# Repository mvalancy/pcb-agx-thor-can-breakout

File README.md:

<picture>
  <source media="(prefers-color-scheme: dark)" srcset="docs/img/hero/pcb-agx-thor-can-breakout-dark.svg">
  
</picture>

# Thor CAN breakout

Passive CAN adapters and printable housings for NVIDIA Jetson AGX Thor. The adapter brings the carrier's CAN bus signals to male DE9 connectors and the remaining J47 signals to an internal I/O header.

[Design review](docs/design-review.md) · [Design packages](releases/README.md) · [Termination & prototyping](docs/termination-and-io.md) · [Assembly guide](ASSEMBLY.md) · [Manufacturing guide](docs/manufacturing.md) · [Validation and open gates](docs/release-checklist.md) · [Local review page](http://localhost:8765/site/)

**A1 engineering prototype — not production qualified.** Both boards pass electrical CAD checks, and the housings pass modeled collision, assembly-path and mesh checks. No physical board or housing has been tested. The exact ribbon/header mating, supplier assembly, CAN operation and transient protection must be verified before connecting an expensive host or ordering 50 units.

## PINOUT proof

© NVIDIA. Direct excerpt from **P4071 A02 concept schematic, sheet 11**. J47 is **Wieson AC2800-0011-022-H0**; read the external contact numbers beside the wires. [Source and capture provenance](docs/pinout-proof.md).

© NVIDIA. The [Jetson Linux r38.2 CAN guide](https://docs.nvidia.com/jetson/archives/r38.2/DeveloperGuide/HR/ControllerAreaNetworkCan.html) independently identifies **CAN0 H/L = 3/5**, **CAN1 H/L = 7/9**, and termination bridges **3–4 / 7–8**. [Full proof, auxiliary mapping and limits](docs/pinout-proof.md). These sources establish documented pins; actual carrier population and all 26 cable conductors still require verification.

## What it does

- Uses the same Wieson **AC2800-0011-022-H0** header identified in Thor's P4071 A02 BOM. Its 26-pad footprint is recovered from NVIDIA's native layout.
- Routes CAN directly to standard CAN DE9 pins: **2 = CAN-L, 7 = CAN-H, 3/6 = ground, 5/shell = shield**. Pins 1/4/8/9 are unconnected; pin 9 supplies no power.
- Adds a **Bourns CDSOT23-SM712 TVS** to each channel. This is a passive breakout, not an isolated repeater or a transceiver board.
- Enables the carrier’s existing **120 Ω termination with JP1 (CAN0) and JP2 (CAN1)**; fit a 2.54 mm jumper cap only at a bus endpoint. Auxiliary power and shield links also remain **open by default**. [Illustrated setup](docs/termination-and-io.md).
- Retains all 26 header signals and adds isolated 2.54 mm prototyping grids, ground and gated 3.3 V/5 V taps. Raw FSI GPIO is firmware-dependent, not a normal Linux GPIO.
- Houses the PCB with heat-set inserts, recessed screw heads, a keyed seam, four broad, recessed M3 corner mounting ears and a padded ribbon clamp with filleted rear supports. The lid carries the pinout, port names, A1 revision and `github.com/mvalancy`.

The TVS is intended to reduce transients; the assembly has no verified surge rating and does not protect against sustained 24 V miswiring. Raw auxiliary I/O has no added protection. See [electrical scope](docs/interface-and-protection.md).

## Choose the right variant

| | Two-port | Four-port engineering variant |
|---|---|---|
| Intended use | AGX Thor FSI CAN0/CAN1 | Generic P4071 A02 full-header investigation |
| Extra channels | Retained on internal J11 for investigation | External ports marked RES2/RES3 |
| IGX compatibility | Not established | **Not established; do not infer it from AURIX net names** |
| PCB | 93 × 90 mm | 177 × 90 mm |
| Housing | 103.2 × 114.2 × 26.8 mm | 187.2 × 114.2 × 26.8 mm |
| Including mounting ears | 149.2 × 114.2 × 26.8 mm | 233.2 × 114.2 × 26.8 mm |
| Prototype pads | 120 isolated pads + gated power taps | 324 isolated pads + gated power taps |
| Schematic | [PDF](exports/2port/schematic.pdf) | [PDF](exports/4port/schematic.pdf) |
| Copper | [Top](exports/2port/pcb-top.svg) · [Bottom](exports/2port/pcb-bottom.svg) | [Top](exports/4port/pcb-top.svg) · [Bottom](exports/4port/pcb-bottom.svg) |
| Native KiCad project | [Two-port](hardware/2port/thor-2port.kicad_pro) | [Four-port](hardware/4port/thor-4port.kicad_pro) |
| Assembly | [Drawing](exports/2port/assembly.svg) · [BOM](exports/2port/bom-review.csv) | [Drawing](exports/4port/assembly.svg) · [BOM](exports/4port/bom-review.csv) |
| Housing dimensions | [Plan](exports/2port/enclosure-plan.svg) | [Plan](exports/4port/enclosure-plan.svg) |
| Check reports | [Electrical](exports/2port/pcb-evidence.json) · [Mechanical](exports/2port/mechanical-checks.json) | [Electrical](exports/4port/pcb-evidence.json) · [Mechanical](exports/4port/mechanical-checks.json) |

The extra channels in the generic schematic do not prove that a particular AGX or IGX carrier populates or supports them. [Carrier compatibility research](research/igx-compatibility.md).

## Termination and room to build

[Termination, AUX pinout, FSI_EXT_GPIO1 limits and prototype wiring](docs/termination-and-io.md) explains every control and usable area. Both power rails stay disconnected until their individual enable shunts are fitted.

## Header, ribbon cable and mating connectors

The cable candidate is **Samtec FFSD-13-D-06.00-01-N**, 152.4 mm long, with two 26-position female connectors: [DigiKey SAM8785-ND](https://www.digikey.com/en/products/detail/samtec-inc/FFSD-13-D-06-00-01-N/3190987). Its fit on the actual Wieson header and pin-for-pin continuity are not yet verified. Do not treat the Samtec SHF alternative footprint as an approved Wieson substitute. [Header audit](research/j47-footprint-audit.md).

The board DE9 is **Assmann A-DS 09 A/KG-T2S / C3127392**. Mating clearance models represent **A-DF 09 LL/Z** female connectors with **A-FT 09** backshells and #4-40 thumbscrews. At 42 mm port pitch, maximum-width hood envelopes leave 7.7 mm between neighbors. Actual screw engagement and hood capture still require a sample. [Connector sourcing](research/connector-sourcing.md) · [Mating audit](research/mating-dsub-clearance.md).

## Print and assemble

The lid uses bold lettering throughout, 4 mm body-text size, enlarged pin numbers and 1 mm diagram strokes. The 0.4 mm recesses retain 2 mm of roof underneath. [Lid layout and clearance evidence](docs/enclosure.md) explain the dimensions and print assumptions; renders show optional light paint fill.

Use one matching base/lid pair and the common ribbon clamp. Print the insert/counterbore and port coupons first. The [assembly guide](ASSEMBLY.md) and [hardware BOM](exports/enclosure-bom.csv) specify six heat-set inserts, four M3 × 20 lid screws, two M3 × 6 clamp screws, PCB washers and silicone pads.

| Printed part | STL | Quantity |
|---|---|---:|
| Two-port base/lid | [Base](exports/2port_base.stl) · [Lid](exports/2port_lid.stl) | One each for two-port |
| Four-port base/lid | [Base](exports/4port_base.stl) · [Lid](exports/4port_lid.stl) | One each for four-port |
| Common ribbon clamp | [Clamp](exports/ribbon_clamp.stl) | 1 |
| Insert/counterbore coupon | [Coupon](exports/fastener_coupon.stl) | Test first |
| DE9 opening coupon | [Coupon](exports/port_coupon.stl) | Test first |

[STEP and 3MF files](exports/README.md) are also supplied. STL/3MF files are bed-oriented; STEP files use assembly coordinates. Mounting ears are 26 mm wide with R4 roots and retain 7 mm thickness. Four M3 holes form a 123.2 × 76 mm pattern on the two-port base or 207.2 × 76 mm on the four-port base. The proposed 10 N / 60 s cable pull test has not been performed. White paint fill is optional and is shown in the renders.

## Manufacturing and release status

**A1 development is published on `main`.** Improvements use development branches and pull requests; merged feature branches are deleted, and plain `dev` follows `main`. Review packages are produced locally and by PR CI. Existing [A0 releases](https://github.com/mvalancy/pcb-agx-thor-can-breakout/releases) are historical and superseded: A1 corrects the CAN pair routing and the enclosure's PCB handedness. Use PCB and housing files from the same commit/manifest. The current 90 mm-deep design also supersedes earlier 65 mm A1 development drafts. [Package structure](releases/README.md).

The [JLCPCB guide](docs/manufacturing.md) explains the Gerber/drill ZIP, SMT-only BOM/CPL and full sourced BOM/CPL. **J1 Wieson procurement/consignment is unresolved**, so this is not a complete turnkey PCBA order. Review placements and supplier DFM before ordering prototypes. No purchase has been made.

Start with 3–5 prototypes. Validate mating and continuity while disconnected from Thor, then check CAN communication, intended bitrates, grounding, protection and housing retention. Proceed toward approximately 50 units only after the [release checklist](docs/release-checklist.md) is closed.

## Local review and reproduction

The [localhost review page](http://localhost:8765/site/) embeds schematic PDFs, PCB layers, dimensions, lid drawings, 3D assemblies and check reports. This link works on the machine running the server; it is not a public web deployment. The site imports the reusable [cad-agent](https://github.com/Valpatel/cad-agent) tools, including the shared finer wheel zoom (four increments cover the former one-increment distance).

Use Python 3.11 or newer, KiCad 10.0.1 and the pinned dependencies. The recorded build used Python 3.12.3; KiCad's Python environment separately supplies `pcbnew`. See the [toolchain record](references/toolchain.json).

```bash
python3 -m venv .venv
.venv/bin/pip install -r requirements.txt
.venv/bin/cad-agent site --serve --port 8765
```

To rebuild and validate the committed routed design:

```bash
.venv/bin/python tools/export_review.py
.venv/bin/python tools/check_electronics.py
# Also run check_can_routing.py, check_fabrication.py and check_prototype.py with KiCad Python.
.venv/bin/python cad/build.py
.venv/bin/python tools/check_mechanics.py
.venv/bin/python tools/check_lid_markings.py
.venv/bin/python tools/render_review.py
.venv/bin/python tools/draw_mechanics.py
.venv/bin/python tools/draw_controls.py
.venv/bin/cad-agent export-3mf
.venv/bin/cad-agent holes
.venv/bin/cad-agent overhangs
.venv/bin/cad-agent inserts cad/joints.yaml --output exports/inserts.json
.venv/bin/cad-agent slice
.venv/bin/python tools/check_lid_slicing.py
.venv/bin/cad-agent view
.venv/bin/python tools/update_evidence.py
.venv/bin/cad-agent report
.venv/bin/python tools/write_readmes.py
.venv/bin/python tools/validate_release.py --record
.venv/bin/python tools/package_release.py
```

`tools/build_electronics.py` regenerates native sources and overwrites layouts unless `--schematic-only` is used. Full electrical regeneration also requires routing, finalization and all checks. [Tool instructions](tools/README.md) · [Iteration history](docs/iterations.md).

## Project structure

| Folder | Contents |
|---|---|
| [hardware](hardware/README.md) | KiCad projects, interface pin map and pinned footprints |
| [cad](cad/README.md) | Parametric housing source and dimensions |
| [exports](exports/README.md) | Manufacturing review, drawing, print and validation files |
| [preview](preview/README.md) | Rendered assembly and lid views |
| [docs](docs/README.md) | Manufacturing, qualification, decisions and progress |
| [research](research/README.md) | Connector and carrier evidence |
| [references](references/README.md) | Source register and toolchain; vendor archives excluded |
| [tools](tools/README.md) | Generation, checks and release packaging |
| [releases](releases/README.md) | Package structure and release notes |
| [.agents](.agents/README.md) | Engineering lessons and review procedures |
| [.github/workflows](.github/workflows/README.md) | CI and prerelease publication |

Folders have READMEs except `.github` itself: GitHub prioritizes its README over this project overview. CI documentation lives in `.github/workflows/README.md`, and validation prevents recreating the overriding index.

## License

Original work is [MIT licensed](LICENSE). KiCad library derivatives retain CC BY-SA 4.0 and the KiCad design exception; see [third-party notices](THIRD_PARTY.md). Full vendor PDFs and logos are not redistributed. The attributed NVIDIA pinout excerpts retain NVIDIA rights and are excluded from the MIT grant. This project is not affiliated with NVIDIA, Samtec, Assmann or JLCPCB.

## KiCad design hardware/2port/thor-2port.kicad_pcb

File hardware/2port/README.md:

<!-- generated by tools/write_readmes.py -->
# 2-port KiCad project

[Project overview](../../README.md) · [Documentation](../../docs/README.md) · [Local design review](http://localhost:8765/site/)

Native source for the documented AGX Thor FSI CAN0/CAN1 interface.

[Open in KiCad](thor-2port.kicad_pro) · [Schematic PDF](../../exports/2port/schematic.pdf) · [Review exports](../../exports/2port/README.md)

The project includes the schematic, routed board, local symbol/footprint tables and native fabrication rules. `evidence-manifest.json` binds checks to these sources. Review the [pinout proof](../../docs/pinout-proof.md) and [protection scope](../../docs/interface-and-protection.md) before modifying the interface.

CAN trunks use 0.25 mm copper with 0.25 mm straight-section spacing and a protected bottom return corridor. This two-layer/ribbon assembly is not controlled 120 Ω impedance or qualified for a maximum data rate. All removable links are open by default.

<details>
<summary>Complete folder index</summary>

| File or folder | Purpose |
|---|---|
| [Thor.kicad_sym](Thor.kicad_sym) | Pinned schematic symbols |
| [evidence-manifest.json](evidence-manifest.json) | Machine-readable design evidence |
| [fp-lib-table](fp-lib-table) | Project support file |
| [sym-lib-table](sym-lib-table) | Project support file |
| [thor-2port.kicad_dru](thor-2port.kicad_dru) | Native fabrication rules |
| [thor-2port.kicad_pcb](thor-2port.kicad_pcb) | Routed native board |
| [thor-2port.kicad_pro](thor-2port.kicad_pro) | KiCad project settings |
| [thor-2port.kicad_sch](thor-2port.kicad_sch) | Native schematic |

</details>

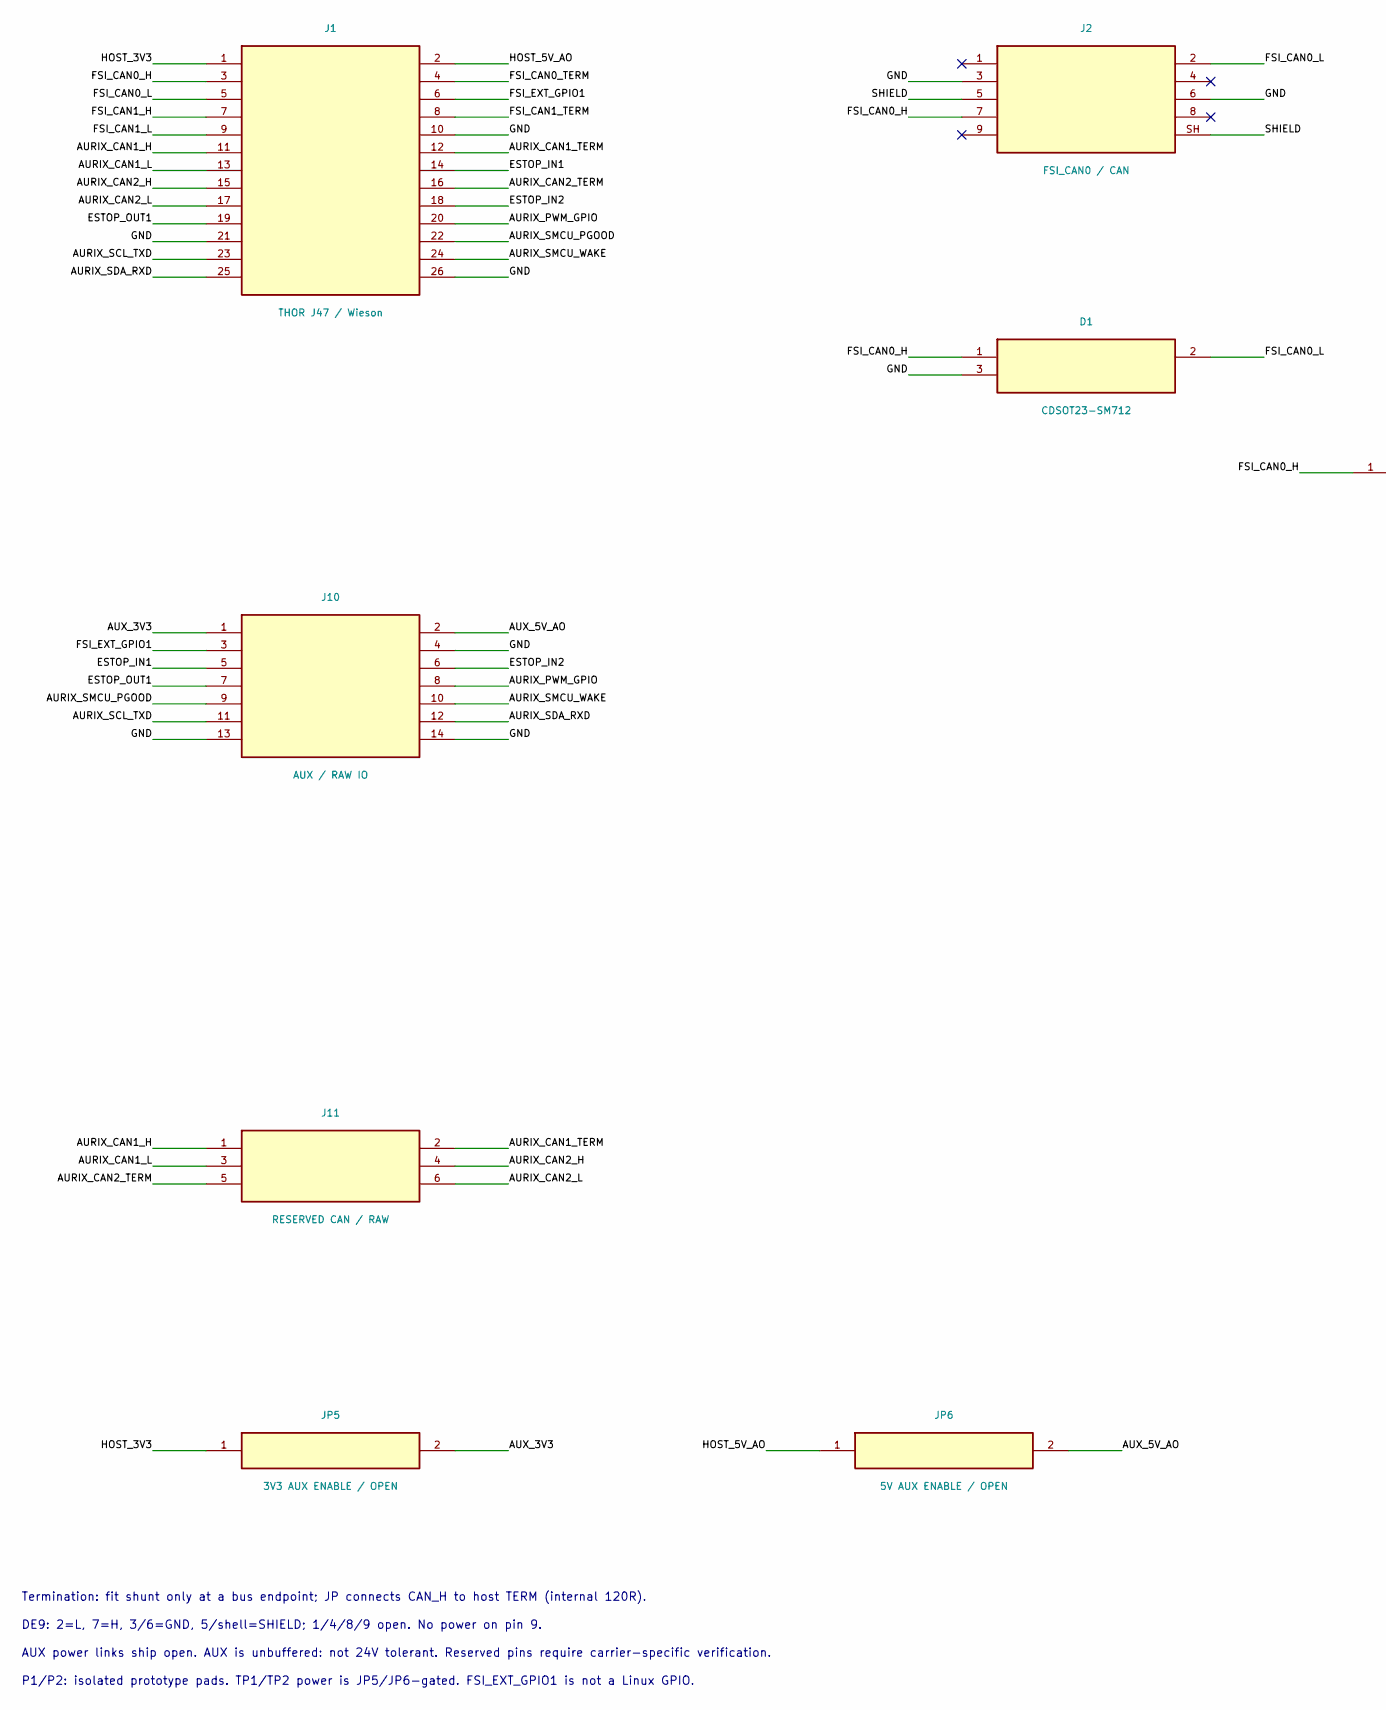
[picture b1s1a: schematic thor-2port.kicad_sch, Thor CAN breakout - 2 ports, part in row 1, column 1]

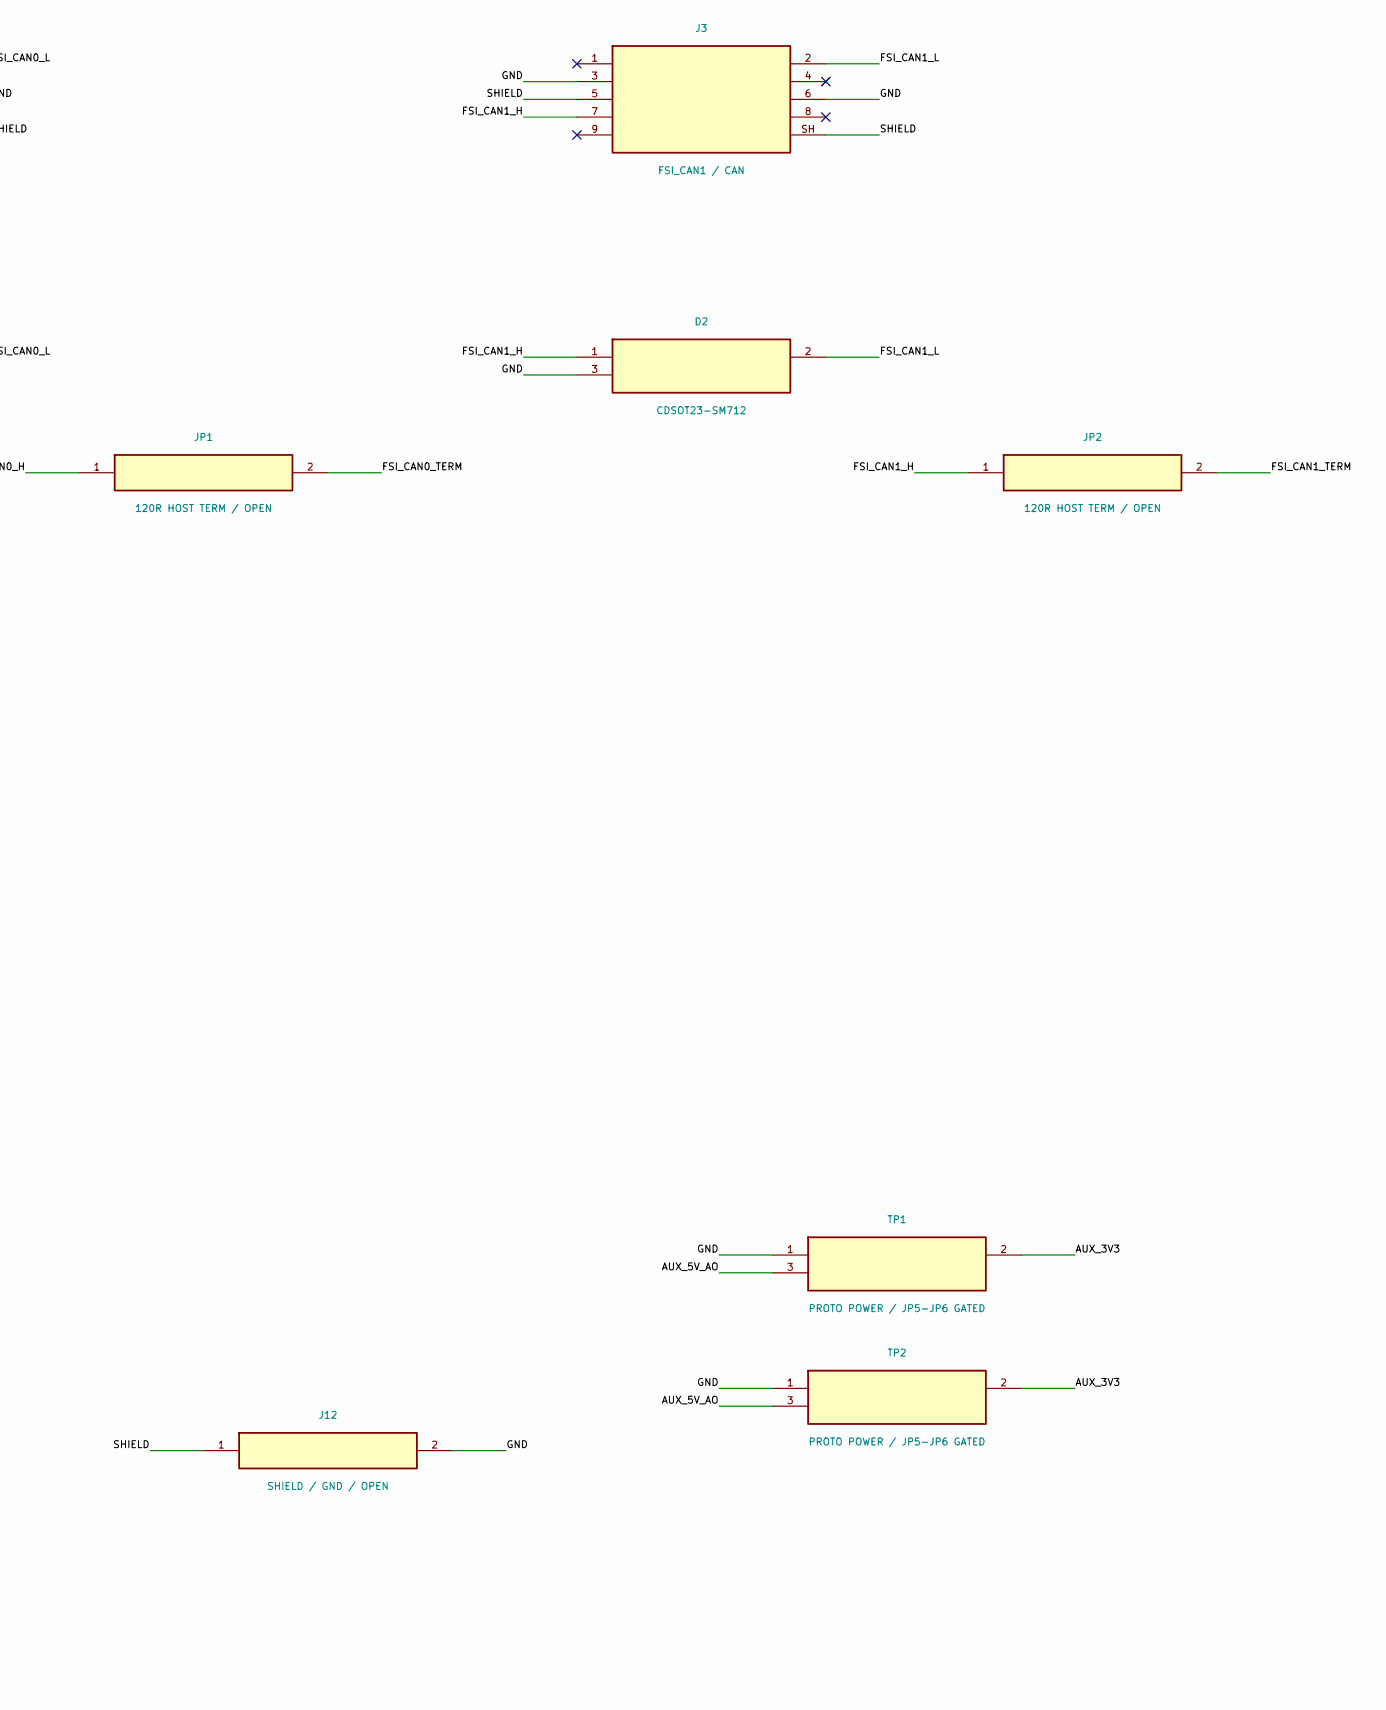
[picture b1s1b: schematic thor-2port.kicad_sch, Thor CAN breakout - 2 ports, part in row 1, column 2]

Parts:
D1, D2: CDSOT23-SM712; SOT-23; MPN CDSOT23-SM712; LCSC C404012
J1: THOR J47 / Wieson; Wieson_AC2800-0011-022-H0; MPN AC2800-0011-022-H0
J2: FSI_CAN0 / CAN; Assmann_A-DS_09_A-KG-T2S; MPN A-DS 09 A/KG-T2S; LCSC C3127392
J3: FSI_CAN1 / CAN; Assmann_A-DS_09_A-KG-T2S; MPN A-DS 09 A/KG-T2S; LCSC C3127392
J10: AUX / RAW IO; PinHeader_2x07_P2.54mm_Vertical; MPN BOOMELE 2.54-2x7P male C71397; LCSC C71397
J11: RESERVED CAN / RAW; PinHeader_2x03_P2.54mm_Vertical; MPN BOOMELE 2.54-2x3P male C65114; LCSC C65114
J12: SHIELD / GND / OPEN; XFCN_PZ254V-11-02P; MPN PZ254V-11-02P; LCSC C492401
JP1, JP2: 120R HOST TERM / OPEN; XFCN_PZ254V-11-02P; MPN PZ254V-11-02P; LCSC C492401
JP5: 3V3 AUX ENABLE / OPEN; XFCN_PZ254V-11-02P; MPN PZ254V-11-02P; LCSC C492401
JP6: 5V AUX ENABLE / OPEN; XFCN_PZ254V-11-02P; MPN PZ254V-11-02P; LCSC C492401
TP1, TP2: PROTO POWER / JP5-JP6 GATED; Prototype_Power_3x3_P2.54

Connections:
/AURIX_CAN1_H: J1.11 (AURIX_CAN1_H), J11.1 (AURIX_CAN1_H)
/AURIX_CAN1_L: J1.13 (AURIX_CAN1_L), J11.3 (AURIX_CAN1_L)
/AURIX_CAN1_TERM: J1.12 (AURIX_CAN1_TERM), J11.2 (AURIX_CAN1_TERM)
/AURIX_CAN2_H: J1.15 (AURIX_CAN2_H), J11.4 (AURIX_CAN2_H)
/AURIX_CAN2_L: J1.17 (AURIX_CAN2_L), J11.6 (AURIX_CAN2_L)
/AURIX_CAN2_TERM: J1.16 (AURIX_CAN2_TERM), J11.5 (AURIX_CAN2_TERM)
/AURIX_PWM_GPIO: J1.20 (AURIX_PWM_GPIO), J10.8 (AURIX_PWM_GPIO)
/AURIX_SCL_TXD: J1.23 (AURIX_SCL_TXD), J10.11 (AURIX_SCL_TXD)
/AURIX_SDA_RXD: J1.25 (AURIX_SDA_RXD), J10.12 (AURIX_SDA_RXD)
/AURIX_SMCU_PGOOD: J1.22 (AURIX_SMCU_PGOOD), J10.9 (AURIX_SMCU_PGOOD)
/AURIX_SMCU_WAKE: J1.24 (AURIX_SMCU_WAKE), J10.10 (AURIX_SMCU_WAKE)
/AUX_3V3: J10.1 (AUX_3V3), JP5.2 (AUX_3V3), TP1.2 (AUX_3V3), TP2.2 (AUX_3V3)
/AUX_5V_AO: J10.2 (AUX_5V_AO), JP6.2 (AUX_5V_AO), TP1.3 (AUX_5V_AO), TP2.3 (AUX_5V_AO)
/ESTOP_IN1: J1.14 (ESTOP_IN1), J10.5 (ESTOP_IN1)
/ESTOP_IN2: J1.18 (ESTOP_IN2), J10.6 (ESTOP_IN2)
/ESTOP_OUT1: J1.19 (ESTOP_OUT1), J10.7 (ESTOP_OUT1)
/FSI_CAN0_H: D1.1 (FSI_CAN0_H), J1.3 (FSI_CAN0_H), J2.7 (FSI_CAN0_H), JP1.1 (FSI_CAN0_H)
/FSI_CAN0_L: D1.2 (FSI_CAN0_L), J1.5 (FSI_CAN0_L), J2.2 (FSI_CAN0_L)
/FSI_CAN0_TERM: J1.4 (FSI_CAN0_TERM), JP1.2 (FSI_CAN0_TERM)
/FSI_CAN1_H: D2.1 (FSI_CAN1_H), J1.7 (FSI_CAN1_H), J3.7 (FSI_CAN1_H), JP2.1 (FSI_CAN1_H)
/FSI_CAN1_L: D2.2 (FSI_CAN1_L), J1.9 (FSI_CAN1_L), J3.2 (FSI_CAN1_L)
/FSI_CAN1_TERM: J1.8 (FSI_CAN1_TERM), JP2.2 (FSI_CAN1_TERM)
/FSI_EXT_GPIO1: J1.6 (FSI_EXT_GPIO1), J10.3 (FSI_EXT_GPIO1)
/GND: D1.3 (GND), D2.3 (GND), J1.10 (GND), J1.21 (GND), J1.26 (GND), J2.3 (GND), J2.6 (GND), J3.3 (GND), J3.6 (GND), J10.4 (GND), J10.13 (GND), J10.14 (GND), J12.2 (GND), TP1.1 (GND), TP2.1 (GND)
/HOST_3V3: J1.1 (HOST_3V3), JP5.1 (HOST_3V3)
/HOST_5V_AO: J1.2 (HOST_5V_AO), JP6.1 (HOST_5V_AO)
/SHIELD: J2.5 (SHIELD), J2.SH (SHIELD), J3.5 (SHIELD), J3.SH (SHIELD), J12.1 (SHIELD)

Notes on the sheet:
Termination: fit shunt only at a bus endpoint; JP connects CAN_H to host TERM (internal 120R).
DE9: 2=L, 7=H, 3/6=GND, 5/shell=SHIELD; 1/4/8/9 open. No power on pin 9.
AUX power links ship open. AUX is unbuffered: not 24V tolerant. Reserved pins require carrier-specific verification.
P1/P2: isolated prototype pads. TP1/TP2 power is JP5/JP6-gated. FSI_EXT_GPIO1 is not a Linux GPIO.

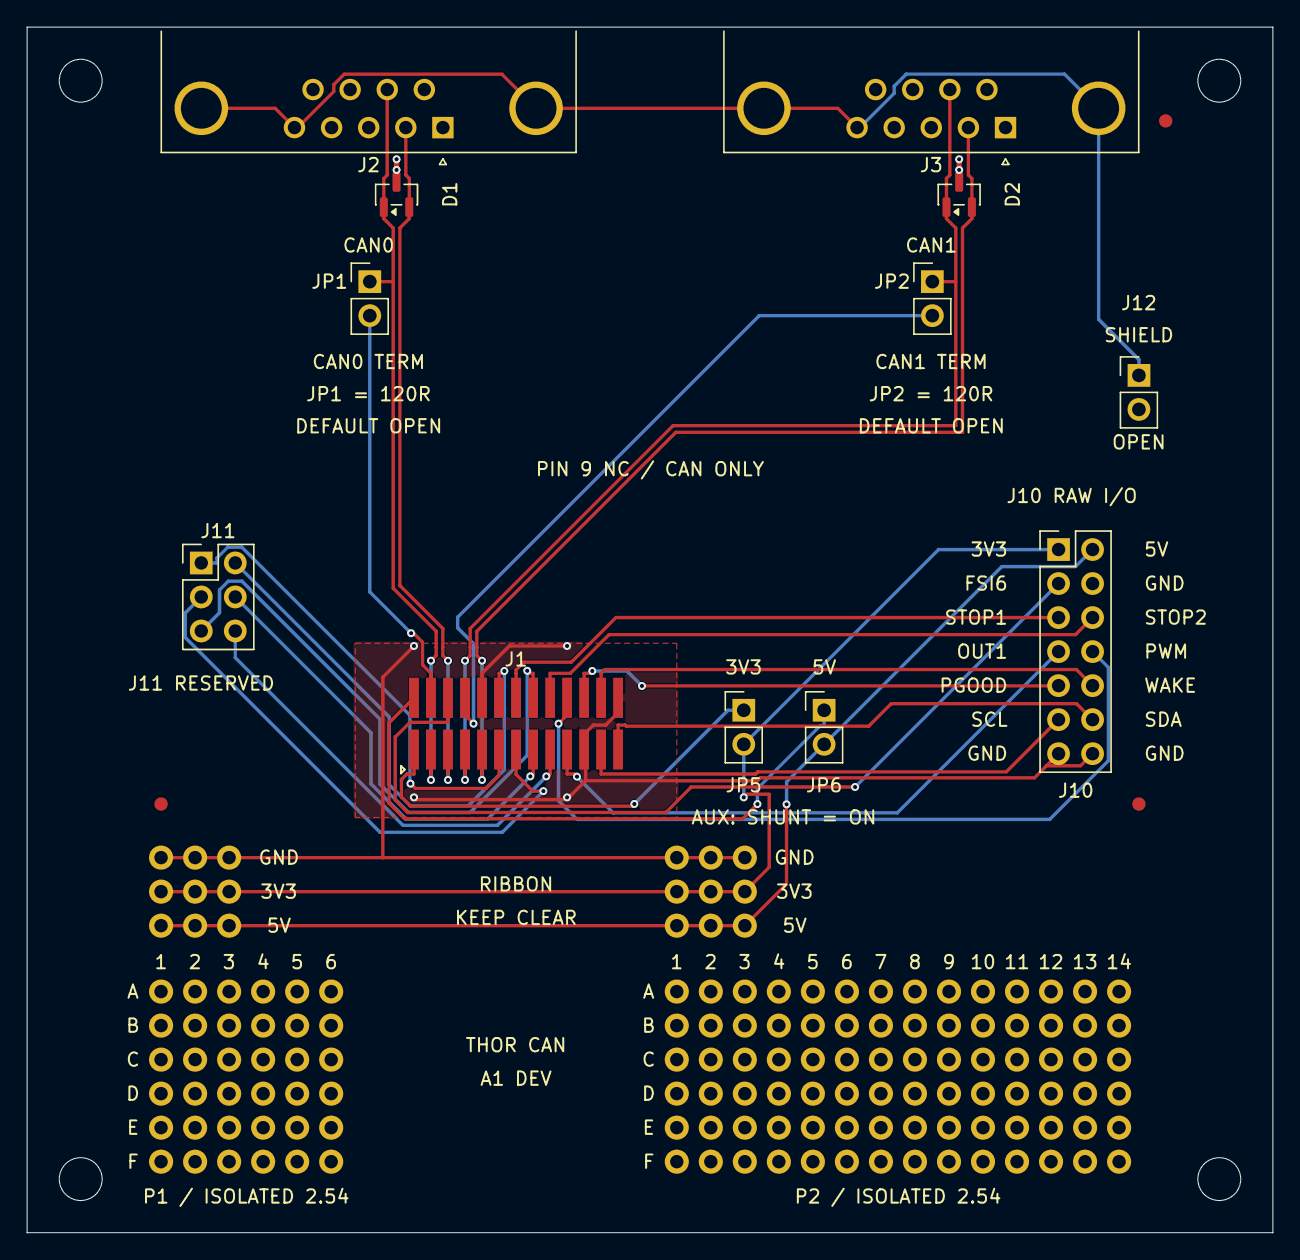
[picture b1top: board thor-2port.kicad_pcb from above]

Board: 2 copper layers, 93.0 x 90.0 mm, 23 parts (0 on the bottom side), 27 nets.

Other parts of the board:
FID1, FID2, FID3: Fiducial_1mm_Mask2mm
H1, H2, H3, H4: M3; MountingHole_3.2mm_M3
P1: ISOLATED PROTOTYPING PADS; Prototype_6x6_P2.54
P2: ISOLATED PROTOTYPING PADS; Prototype_14x6_P2.54
